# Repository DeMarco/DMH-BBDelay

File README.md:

# DMH-BBDelay
Bucket Brigade Delay in Kosmo Format

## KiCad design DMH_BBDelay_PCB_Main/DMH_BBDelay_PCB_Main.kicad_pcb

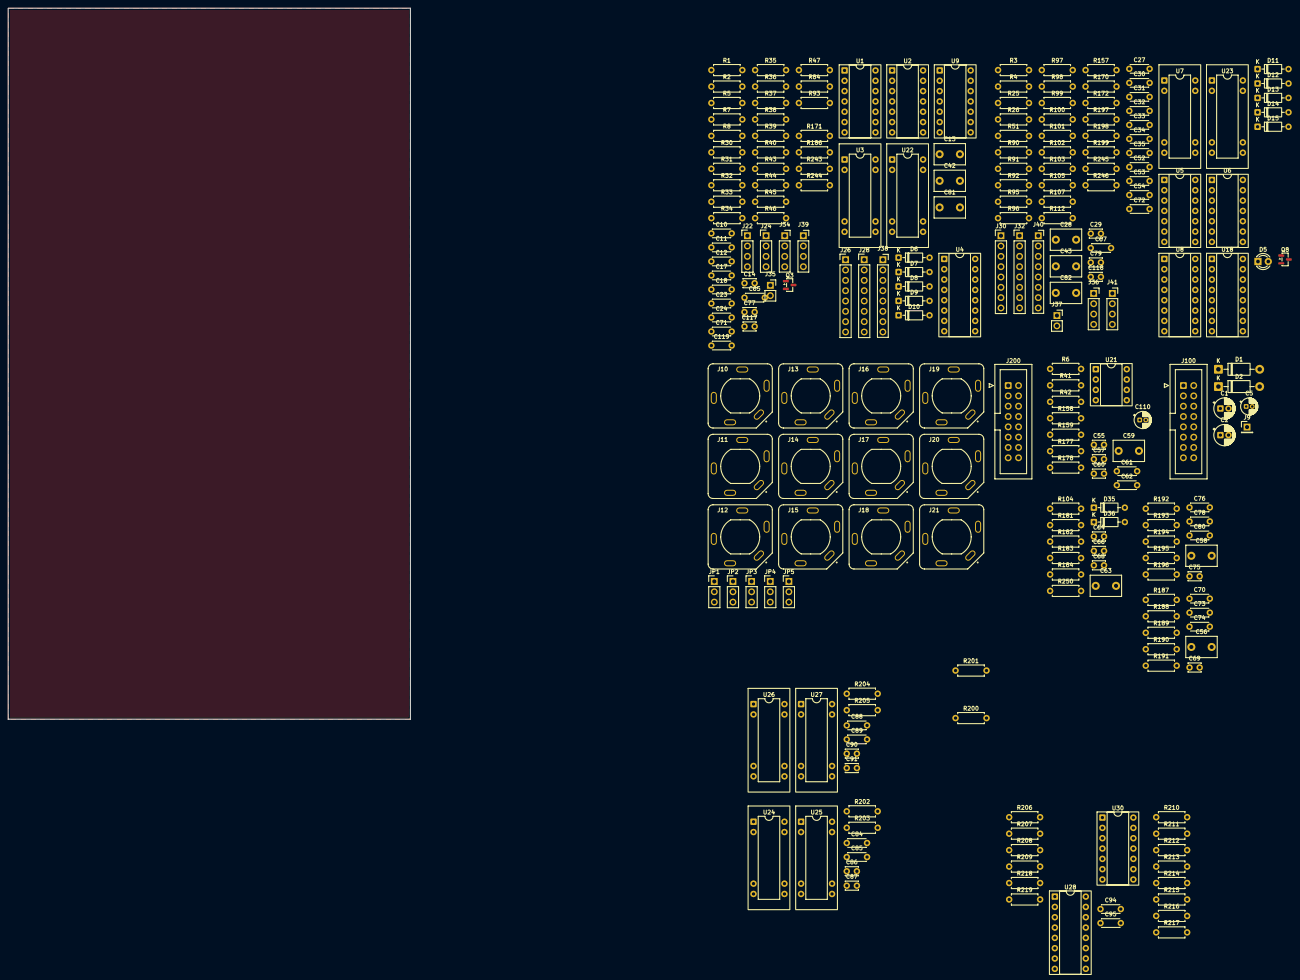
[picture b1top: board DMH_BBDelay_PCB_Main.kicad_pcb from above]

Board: 2 copper layers, 99.0 x 175.0 mm, 236 parts (0 on the bottom side), 160 nets, no tracks yet.

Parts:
C1, C2: 47uF; CP_Radial_D5.0mm_P2.00mm
C5: 47uF; CP_Radial_D4.0mm_P1.50mm
C10, C11, C12, C18, C23, C24, C27, C30, C31, C33, C34, C35, C52, C53, C54, C61, C62, C65, C67, C71, C72, C84, C85, C88, C89, C94, C95: 100nF; C_Disc_D4.3mm_W1.9mm_P5.00mm
C13, C28, C42, C43, C56, C58, C59, C63, C81, C82: 1uF Film; C_Disc_D7.5mm_W5.0mm_P5.00mm
C14, C29: 220pF; C_Disc_D3.0mm_W2.0mm_P2.50mm
C17, C32: 15nF; C_Disc_D4.3mm_W1.9mm_P5.00mm
C55, C68: 150p; C_Disc_D3.0mm_W2.0mm_P2.50mm
C57, C60, C64, C66: 1.5nF; C_Disc_D3.0mm_W2.0mm_P2.50mm
C69, C75: 100p; C_Disc_D3.0mm_W2.0mm_P2.50mm
C70, C80: 1.5nF; C_Disc_D4.3mm_W1.9mm_P5.00mm
C73, C74, C76, C78: 1nF; C_Disc_D4.3mm_W1.9mm_P5.00mm
C77, C79, C86, C87, C90, C91: 470pF; C_Disc_D3.0mm_W2.0mm_P2.50mm
C110: 4.7uF; CP_Radial_D4.0mm_P1.50mm
C117, C118: 100pF; C_Disc_D3.0mm_W2.0mm_P2.50mm
C119: 3.3uF; C_Disc_D4.3mm_W1.9mm_P5.00mm
D1, D2: 1N5819; D_DO-41_SOD81_P10.16mm_Horizontal
D5: LED_Blue; LED_D3.0mm
D6, D15, D35, D36: 1N4148; D_DO-35_SOD27_P7.62mm_Horizontal
D7, D10, D12, D14: ZPD5v1; D_DO-35_SOD27_P7.62mm_Horizontal
D8, D9, D11, D13: BAT85; D_DO-35_SOD27_P7.62mm_Horizontal
J9: Conn_01x01; PinHeader_1x01_P2.54mm_Vertical
J10, J11, J12, J13, J14, J15, J16, J17, J18, J19, J20, J21: TRS_Jack_6.35mm_Sw; CUI_SJ-63083D
J22, J24: Conn_01x04; PinHeader_1x04_P2.54mm_Vertical
J26, J28, J30, J32: Conn_01x08; PinHeader_1x08_P2.54mm_Vertical
J34, J36, J39, J41: Conn_01x04; PinSocket_1x04_P2.54mm_Vertical
J35, J37: Conn_01x02; PinSocket_1x02_P2.54mm_Vertical
J38, J40: Conn_01x08; PinSocket_1x08_P2.54mm_Vertical
J100: IDC_02x08; IDC-Header_2x08_P2.54mm_Vertical_Eurorack
J200: IDC_02x08; IDC-Header_2x08_P2.54mm_Vertical_BackBone
JP1, JP2, JP3, JP4, JP5: Jumper_3_Bridged12; PinHeader_1x03_P2.54mm_Vertical
Q3, Q8: J113; SOT-23
R1, R3: 220k; R_Axial_DIN0207_L6.3mm_D2.5mm_P7.62mm_Horizontal
R2, R4, R5, R6, R25, R32, R33, R34, R37, R95, R96, R97, R101, R104, R170, R171, R172, R178, R183, R218, R219, R243, R246: 100k; R_Axial_DIN0207_L6.3mm_D2.5mm_P7.62mm_Horizontal
R7, R90: 3k3; R_Axial_DIN0207_L6.3mm_D2.5mm_P7.62mm_Horizontal
R8, R26: 2k2; R_Axial_DIN0207_L6.3mm_D2.5mm_P7.62mm_Horizontal
R30, R157: 4k7; R_Axial_DIN0207_L6.3mm_D2.5mm_P7.62mm_Horizontal
R31, R159, R182: 56k; R_Axial_DIN0207_L6.3mm_D2.5mm_P7.62mm_Horizontal
R35, R99: 5k6; R_Axial_DIN0207_L6.3mm_D2.5mm_P7.62mm_Horizontal
R36, R40, R44, R45, R51, R98, R102, R105: 10k; R_Axial_DIN0207_L6.3mm_D2.5mm_P7.62mm_Horizontal
R38: 14k; R_Axial_DIN0207_L6.3mm_D2.5mm_P7.62mm_Horizontal
R39, R92: 1M; R_Axial_DIN0207_L6.3mm_D2.5mm_P7.62mm_Horizontal
R41, R42, R200, R201, R202, R203, R204, R205, R244, R245: 20k; R_Axial_DIN0207_L6.3mm_D2.5mm_P7.62mm_Horizontal
R43, R84, R100, R112, R250: 1k; R_Axial_DIN0207_L6.3mm_D2.5mm_P7.62mm_Horizontal
R46, R47, R91, R103, R107, R189, R195: 39k; R_Axial_DIN0207_L6.3mm_D2.5mm_P7.62mm_Horizontal
R93: 15k8; R_Axial_DIN0207_L6.3mm_D2.5mm_P7.62mm_Horizontal
R158, R181: 47k; R_Axial_DIN0207_L6.3mm_D2.5mm_P7.62mm_Horizontal
R177, R184, R188, R196, R197, R207, R209, R211, R213, R215: 33k; R_Axial_DIN0207_L6.3mm_D2.5mm_P7.62mm_Horizontal
R186, R206, R208, R210, R212, R214: 6k8; R_Axial_DIN0207_L6.3mm_D2.5mm_P7.62mm_Horizontal
R187, R192: 120k; R_Axial_DIN0207_L6.3mm_D2.5mm_P7.62mm_Horizontal
R190, R191, R193, R194: 43k; R_Axial_DIN0207_L6.3mm_D2.5mm_P7.62mm_Horizontal
R198, R199, R216, R217: 75R; R_Axial_DIN0207_L6.3mm_D2.5mm_P7.62mm_Horizontal
U1, U2, U5, U6, U30: TL074; DIP-14_W7.62mm_Socket
U3, U7, U22, U23, U24, U25, U26, U27: V3205; DIP-8-16_W7.62mm_Socket
U4, U8: CD4046; DIP-16_W7.62mm_Socket
U9: 40106; DIP-14_W7.62mm_Socket
U18, U28: CD4053B; DIP-16_W7.62mm_Socket
U21: TL072; DIP-8_W7.62mm_Socket

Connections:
+5V: C5.1, C12.2, C18.1, C27.2, C35.2, C52.1, C71.1, C72.2, C84.1, C85.1, C88.1, C89.1, J22.1, J100.6a, J100.6b, R30.2, R41.2, R197.2, R207.2, R209.2, R211.2, R213.2, R215.2, U3.5 (Vdd), U4.14 (SigIn), U4.16 (VDD), U7.5 (Vdd), U8.14 (SigIn), U8.16 (VDD), U9.14 (VDD), U22.5 (Vdd), U23.5 (Vdd), U24.5 (Vdd), U25.5 (Vdd), U26.5 (Vdd), U27.5 (Vdd)
+12V: C2.1, C10.1, C23.1, C30.1, C33.1, C53.1, C61.1, C65.1, C94.1, D2.1 (K), J22.2, J35.1, J37.1, J39.2, J41.2, R37.1, R97.1, R157.1, R170.2, R218.2, R219.2, U1.4 (V+), U2.4 (V+), U5.4 (V+), U6.4 (V+), U18.16 (VDD), U21.8 (V+), U28.16 (VDD), U30.4 (V+)
-12V: C1.2, C11.2, C24.2, C31.2, C34.2, C54.1, C62.2, C67.2, C95.1, D1.2 (A), J22.3, J35.2, J37.2, J39.3, J41.3, R46.2, R93.1, R103.2, U1.11 (V-), U2.11 (V-), U5.11 (V-), U6.11 (V-), U18.7 (VEE), U21.4 (V-), U28.7 (VEE), U30.11 (V-)
/Core Circuit A/Input Filter A/Out: C55.2, R178.2, U21.1, U28.12 (A0)
/Core Circuit A/VCXF_DW_A/Out_X: C81.1, J38.8
/Core Circuit B/Input Filter B/In: C118.2, R90.2, R250.1, U5.7
/Core Circuit B/Input Filter B/Out: C68.2, R183.2, U7.7 (In), U21.7
/Core Circuit B/Output Filter B/In: C58.1, R246.2, U6.8
/Core Circuit B/VCXF_DW_B/Out_X: C82.1, J40.8
A_In_m: C42.1, J10.T (3), JP1.3 (B), R1.2
BBD_A1_Out_m: R186.1, U3.4 (Out2), U28.5 (C0)
BBD_A4_Out_m: U25.4 (Out2), U28.3 (C1)
B_In_m: C43.1, J16.T (3), R3.2
Clock_A_Inv_m: C14.1, J28.1, R198.2, U3.2 (CP2), U22.6 (CP1), U24.2 (CP2), U25.6 (CP1)
Clock_A_m: J26.4, U4.3 (RefIn), U4.4 (FOUT), U30.3 (+)
Clock_B_Inv_m: C29.1, J32.1, R217.2, U7.2 (CP2), U23.6 (CP1), U26.2 (CP2), U27.6 (CP1)
Clock_B_m: J30.4, U8.4 (FOUT)
Clock_Cap1_B_m: J30.5, U8.6 (C1)
Clock_Cap2_B_m: J30.6, U8.7 (C2)
DW_A_CV_In_m: J12.T (3), J28.7, J38.5, JP2.3 (B)
DW_A_CV_Pot_m: J28.6, J38.6
DW_A_Out_m: J11.T (3), J200.2, R84.2
DW_A_Pot_m: J28.8, J38.7
DW_B_CV_In_m: J18.T (3), J32.7, J40.5
DW_B_CV_Pot_m: J32.6, J40.6
DW_B_Out_m: J17.T (3), J200.10, R112.2
DW_B_Pot_m: J32.8, J40.7
Dry_A_Buff_m: C59.1, J26.3, J38.1, R6.2, U1.1, U1.2 (-), U28.13 (A1)
Dry_B_Buff_Sw_m: R25.2, U18.4 (C)
Dry_B_Buff_m: J30.3, U5.1, U5.2 (-), U18.3 (C1)
FB_A_CV_In_m: J14.T (3), J28.3, JP4.3 (B)
FB_A_CV_Proc_m: J28.2, J34.2
FB_B_CV_In_m: J20.T (3), J32.3
FB_B_CV_Proc_m: J32.2, J36.2
GND: C1.1, C2.2, C5.2, C10.2, C11.1, C12.1, C17.1, C18.2, C23.2, C24.1, C27.1, C30.2, C31.1, C32.1, C33.2, C34.1, C35.1, C52.2, C53.2, C54.2, C57.1, C60.1, C61.2, C62.1, C64.1, C65.2, C66.1, C67.1, C70.1, C71.2, C72.1, C73.1, C74.1, C76.1, C77.1, C78.1, C79.1, C80.1, C84.2, C85.2, C86.1, C87.1, C88.2, C89.2, C90.1, C91.1, C94.2, C95.2, C110.2, C119.1, D7.2 (A), D8.2 (A), D9.2 (A), D10.2 (A), D11.2 (A), D12.2 (A), D13.2 (A), D14.2 (A), D35.2 (A), D36.1 (K), J9.1 (Pin_1_1), J10.S (1), J11.S (1), J12.S (1), J13.S (1), J14.S (1), J15.S (1), J16.S (1), J17.S (1), J18.S (1), J19.S (1), J20.S (1), J21.S (1), J22.4, J24.1, J24.2, J24.3, J24.4, J30.1, J34.4, J36.4, J39.1, J39.4, J41.1, J41.4, J100.2a, J100.2b, J100.3a, J100.3b, J100.4a, J100.4b, J200.7, J200.8, J200.15, J200.16, R1.1, R2.1, R3.1, R4.1, R6.1, R31.1, R32.1, R33.1, R35.1, R36.1, R38.1, R39.1, R42.1, R91.1, R92.1, R95.1, R96.1, R98.1, R99.1, R104.1, R171.1, R172.1, R200.1, R201.1, R202.1, R203.1, R204.1, R205.1, R244.1, R245.1, U1.5 (+), U2.3 (+), U2.5 (+), U2.12 (+), U3.1 (GND), U4.8 (VSS), U5.5 (+), U6.3 (+), U6.5 (+), U6.12 (+), U7.1 (GND), U8.8 (VSS), U9.5, U9.7 (VSS), U9.9, U18.6 (INH), U18.8 (VSS), U21.3 (+), U22.1 (GND), U23.1 (GND), U24.1 (GND), U25.1 (GND), U26.1 (GND), U27.1 (GND), U28.6 (INH), U28.8 (VSS)
In_Mix_A_m: C117.1, R5.2, R7.1, R8.1, R93.2, U1.6 (-)
Inhibit_A_CV_m: J15.T (3), JP5.3 (B), R40.1, R171.2
Inhibit_B_CV_m: J21.T (3), R51.1, R172.2
Link_Sw_m: J30.2, U8.3 (RefIn), U30.12 (+)
unnamed: C56.2, R191.1
unnamed: C57.2, R159.2, R177.1, R178.1
unnamed: C58.2, R193.1
unnamed: C59.2, R158.1
unnamed: C60.2, R158.2, R159.1
unnamed: C63.2, R181.1
unnamed: C64.2, R181.2, R182.1
unnamed: C66.2, R182.2, R183.1, R184.1
unnamed: C70.2, R187.1, R188.1, R189.2
unnamed: C73.2, R189.1, R190.2
unnamed: C74.2, R190.1, R191.2
unnamed: C76.2, R193.2, R194.1
unnamed: C78.2, R194.2, R195.1
unnamed: C80.2, R192.1, R195.2, R196.1
unnamed: C81.2, R84.1
unnamed: C82.2, R112.1
unnamed: D1.1 (K), J100.1a, J100.1b
unnamed: D2.2 (A), J100.5a, J100.5b
unnamed: D5.2 (A), R157.2
unnamed: D6.2 (A), Q3.3 (G), R34.1
unnamed: D6.1 (K), U1.14
unnamed: D7.1 (K), D8.1 (K), R40.2, U9.11
unnamed: D9.1 (K), D10.1 (K), R43.1, U4.9 (VCOin)
unnamed: D11.1 (K), D12.1 (K), R51.2, U9.3
unnamed: D13.1 (K), D14.1 (K), R100.1, U8.9 (VCOin)
unnamed: D15.2 (A), Q8.3 (G), R101.1
unnamed: D15.1 (K), U5.14
unnamed: C63.1, D35.1 (K), D36.2 (A), R104.2, R250.2
unnamed: J10.TN (2), J200.1
unnamed: J12.TN (2), J200.3
unnamed: J13.TN (2), J200.4
unnamed: J14.TN (2), J200.5
unnamed: J15.TN (2), J200.6
unnamed: J16.TN (2), JP1.2 (C)
unnamed: J18.TN (2), JP2.2 (C)
unnamed: J19.TN (2), JP3.2 (C)
unnamed: J20.TN (2), JP4.2 (C)
unnamed: J21.TN (2), JP5.2 (C)
unnamed: J100.7a, J100.7b
unnamed: J100.8a, J100.8b
unnamed: J200.9, JP1.1 (A)
unnamed: J200.11, JP2.1 (A)
unnamed: J200.12, JP3.1 (A)
unnamed: J200.13, JP4.1 (A)
unnamed: J200.14, JP5.1 (A)
unnamed: Q3.1 (D), R34.2, U1.8, U1.9 (-)
unnamed: C17.2, Q3.2 (S), U2.10 (+)
unnamed: Q8.1 (D), R101.2, U5.8, U5.9 (-)
unnamed: C32.2, Q8.2 (S), U6.10 (+)
unnamed: R43.2, R44.1, U2.1
unnamed: R45.2, R47.1, U2.7
unnamed: R100.2, R102.1, U6.1
unnamed: R105.2, R107.1, U6.7
unnamed: C42.2, R2.2, U1.3 (+)
unnamed: C13.2, R33.2, U1.10 (+)
unnamed: C14.2, R35.2, U1.12 (+)
unnamed: R36.2, R37.2, U1.13 (-)
unnamed: R44.2, R45.1, R46.1, U2.2 (-)
unnamed: R243.1, R244.2, U2.9 (-)
unnamed: C69.1, R188.2, U2.13 (-)
unnamed: C117.2, R7.2, U1.7, U3.7 (In)
unnamed: U4.5 (Inh), U9.12
unnamed: R38.2, U4.11 (R1)
unnamed: R39.2, U4.12 (R2)
unnamed: C43.2, R4.2, U5.3 (+)
unnamed: C118.1, R25.1, R26.1, R90.1, U5.6 (-)
unnamed: C28.2, R96.2, U5.10 (+)
unnamed: C29.2, R99.2, U5.12 (+)
unnamed: R97.2, R98.2, U5.13 (-)
unnamed: R102.2, R103.1, R105.1, U6.2 (-)
unnamed: R245.2, R246.1, U6.9 (-)
unnamed: C75.1, R196.2, U6.13 (-)
unnamed: R210.1, U7.4 (Out2)
unnamed: U8.5 (Inh), U9.2
unnamed: R91.2, U8.11 (R1)
unnamed: R92.2, U8.12 (R2)
unnamed: U9.1, U9.4
unnamed: U9.10, U9.13
unnamed: C55.1, R177.2, U21.2 (-)
unnamed: C68.1, R184.2, U21.6 (-)
unnamed: R199.2, U3.6 (CP1), U22.2 (CP2), U24.6 (CP1), U25.2 (CP2)
unnamed: C77.2, R186.2, R197.1, R200.2, U22.7 (In)
unnamed: R206.1, U22.4 (Out2)
unnamed: R216.2, U7.6 (CP1), U23.2 (CP2), U26.6 (CP1), U27.2 (CP2)
unnamed: C79.2, R201.2, R210.2, R211.1, U23.7 (In)
unnamed: R214.1, U23.4 (Out2)
unnamed: C86.2, R202.2, R206.2, R207.1, U24.7 (In)
unnamed: R208.1, U24.4 (Out2)
unnamed: C87.2, R203.2, R208.2, R209.1, U25.7 (In)
unnamed: C90.2, R204.2, R214.2, R215.1, U26.7 (In)
unnamed: R212.1, U26.4 (Out2)
unnamed: C91.2, R205.2, R212.2, R213.1, U27.7 (In)
unnamed: C28.1, R95.2, U27.4 (Out2)
unnamed: R5.1, U28.14 (A)
unnamed: R199.1, U30.1, U30.2 (-)
unnamed: U4.2 (PC1), U30.5 (+)
unnamed: R198.1, U30.6 (-), U30.7
unnamed: U8.2 (PC1), U30.10 (+)
unnamed: R217.1, U30.8, U30.9 (-)
unnamed: R216.1, U30.13 (-), U30.14
OF_A_In_m: C56.1, R243.2, U2.8, U28.1 (B1)
OF_A_Out_m: C69.2, R187.2, U2.14, U28.2 (B0)
PP_Sw_p2_m: J26.2, J40.1
PP_Sw_p5_m: D5.1 (K), J26.1, R170.1, U18.9 (S3), U18.10 (S2), U18.11 (S1)
Ref_2v5: C110.1, R41.1, R42.2, U21.5 (+)
Rng_A_Sw_p1_m: J26.6, R219.1, U28.9 (S3)
Rng_A_Sw_p3_m: J26.5, R218.1, U28.10 (S2), U28.11 (S1)
SH_A_In_m: C13.1, R32.2, U28.4 (C)
Time_A_CV_In_m: J13.T (3), J28.5, JP3.3 (B)
Time_A_CV_Proc_m: J28.4, R47.2, U2.6 (-)
Time_B_CV_In_m: J19.T (3), J32.5
Time_B_CV_Proc_m: J32.4, R107.2, U6.6 (-)
VCA_FB_A_In_m: J34.1, U18.14 (A)
VCA_FB_A_Out_m: J34.3, R8.2
VCA_FB_B_In_m: J36.1, U18.15 (B)
VCA_FB_B_Out_m: J36.3, R26.2
VGG_m: C119.2, R30.1, R31.2, U3.8 (Vgg), U7.8 (Vgg), U22.8 (Vgg), U23.8 (Vgg), U24.8 (Vgg), U25.8 (Vgg), U26.8 (Vgg), U27.8 (Vgg)
Wet_A_Out_m: J26.7, U18.2 (B0), U18.13 (A1), U28.15 (B)
Wet_A_TC_Out_m: J26.8, J38.3
Wet_B_Out_m: C75.2, J30.7, R192.2, U6.14, U18.1 (B1), U18.12 (A0)
Wet_B_TC_Out_m: J30.8, J40.3

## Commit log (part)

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2025-12-26 Created Panel project
    ... and did initial design
2025-12-26 Update SynthStuff
2025-12-27 FInalized panel design
2025-12-28 Added LEDs and Link switch
2025-12-29 Added tone knob
    ... by making Input Gain switch to span both channels. Also added a center Linked LED
2026-02-22 Centralized library
2026-05-27 KiCad 10
2026-06-28 Replaced Clock Sync with Inhibit input and Range
2026-06-28 Started main PCB project
